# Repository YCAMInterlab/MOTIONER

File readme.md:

# MOTIONER

## Open source low cost inertial motion capture system.

MOTIONER is a low cost inertial motion capture system developed for Reactor for Awareness in Motion(RAM) project at Yamaguchi Center for Arts in Media (YCAM). Using MOTIONER, you can capture, record and playback body movements, and send the data via OSC messages over a network. MOTIONER is designed to work with RAM Dance Toolkit using openFrameworks, and will work with creative coding environments that provide OSC. MOTIONER is developed in collaboration with Yoko Ando (The Forsythe Company) and other dancers. MOTIONER is a light weight, low-stress, and low latency system. Because it's an inertial system, the sensors can be attached either inside or on the outside of clothing.

For more details, please see [MOTIONER wiki](https://github.com/YCAMInterlab/MOTIONER/wiki/)

詳しい情報は[MOTIONER wiki](https://github.com/YCAMInterlab/MOTIONER/wiki/)を参照してください。

## Licenses

### Application
MOTIONER software by YCAM InterLab and Yoshito Onishi is licensed under the 
[Apache License, Version2.0](http://www.apache.org/licenses/LICENSE-2.0.html)

    Copyright 2012-2013 YCAMInterLab and Yoshito Onishi

    Licensed under the Apache License, Version 2.0 (the "License");
    you may not use this file except in compliance with the License.
    You may obtain a copy of the License at

       http://www.apache.org/licenses/LICENSE-2.0

    Unless required by applicable law or agreed to in writing, software
    distributed under the License is distributed on an "AS IS" BASIS,
    WITHOUT WARRANTIES OR CONDITIONS OF ANY KIND, either express or implied.
    See the License for the specific language governing permissions and
    limitations under the License.

### Arduino, Processing sketch and mbed code

Copyright 2012-2013 YCAMInterLab and Yoshito Onishi

MOTIONER Arduino, Processing sketch and mbed code by YCAM InterLab and Yoshito Onishi are licensed under the 
[GNU GPL(General Public License) v3.0](http://www.gnu.org/licenses/gpl.html)

### Hardware

<br /><span xmlns:dct="http://purl.org/dc/terms/" property="dct:title">MOTIONER hardware related documents (Schematics, Eagle files, Solder Stencil Mask, Drawing of MOTIONER base, MOTIONER pcb board, vacuum case and strap)</span> by <a xmlns:cc="http://creativecommons.org/ns#" href="http://interlab.ycam.jp/projects/ram" property="cc:attributionName" rel="cc:attributionURL">YCAM InterLab, Yoshito Onishi</a> is licensed under a <a rel="license" href="http://creativecommons.org/licenses/by-sa/4.0/">Creative Commons Attribution-ShareAlike 4.0 International License</a>.

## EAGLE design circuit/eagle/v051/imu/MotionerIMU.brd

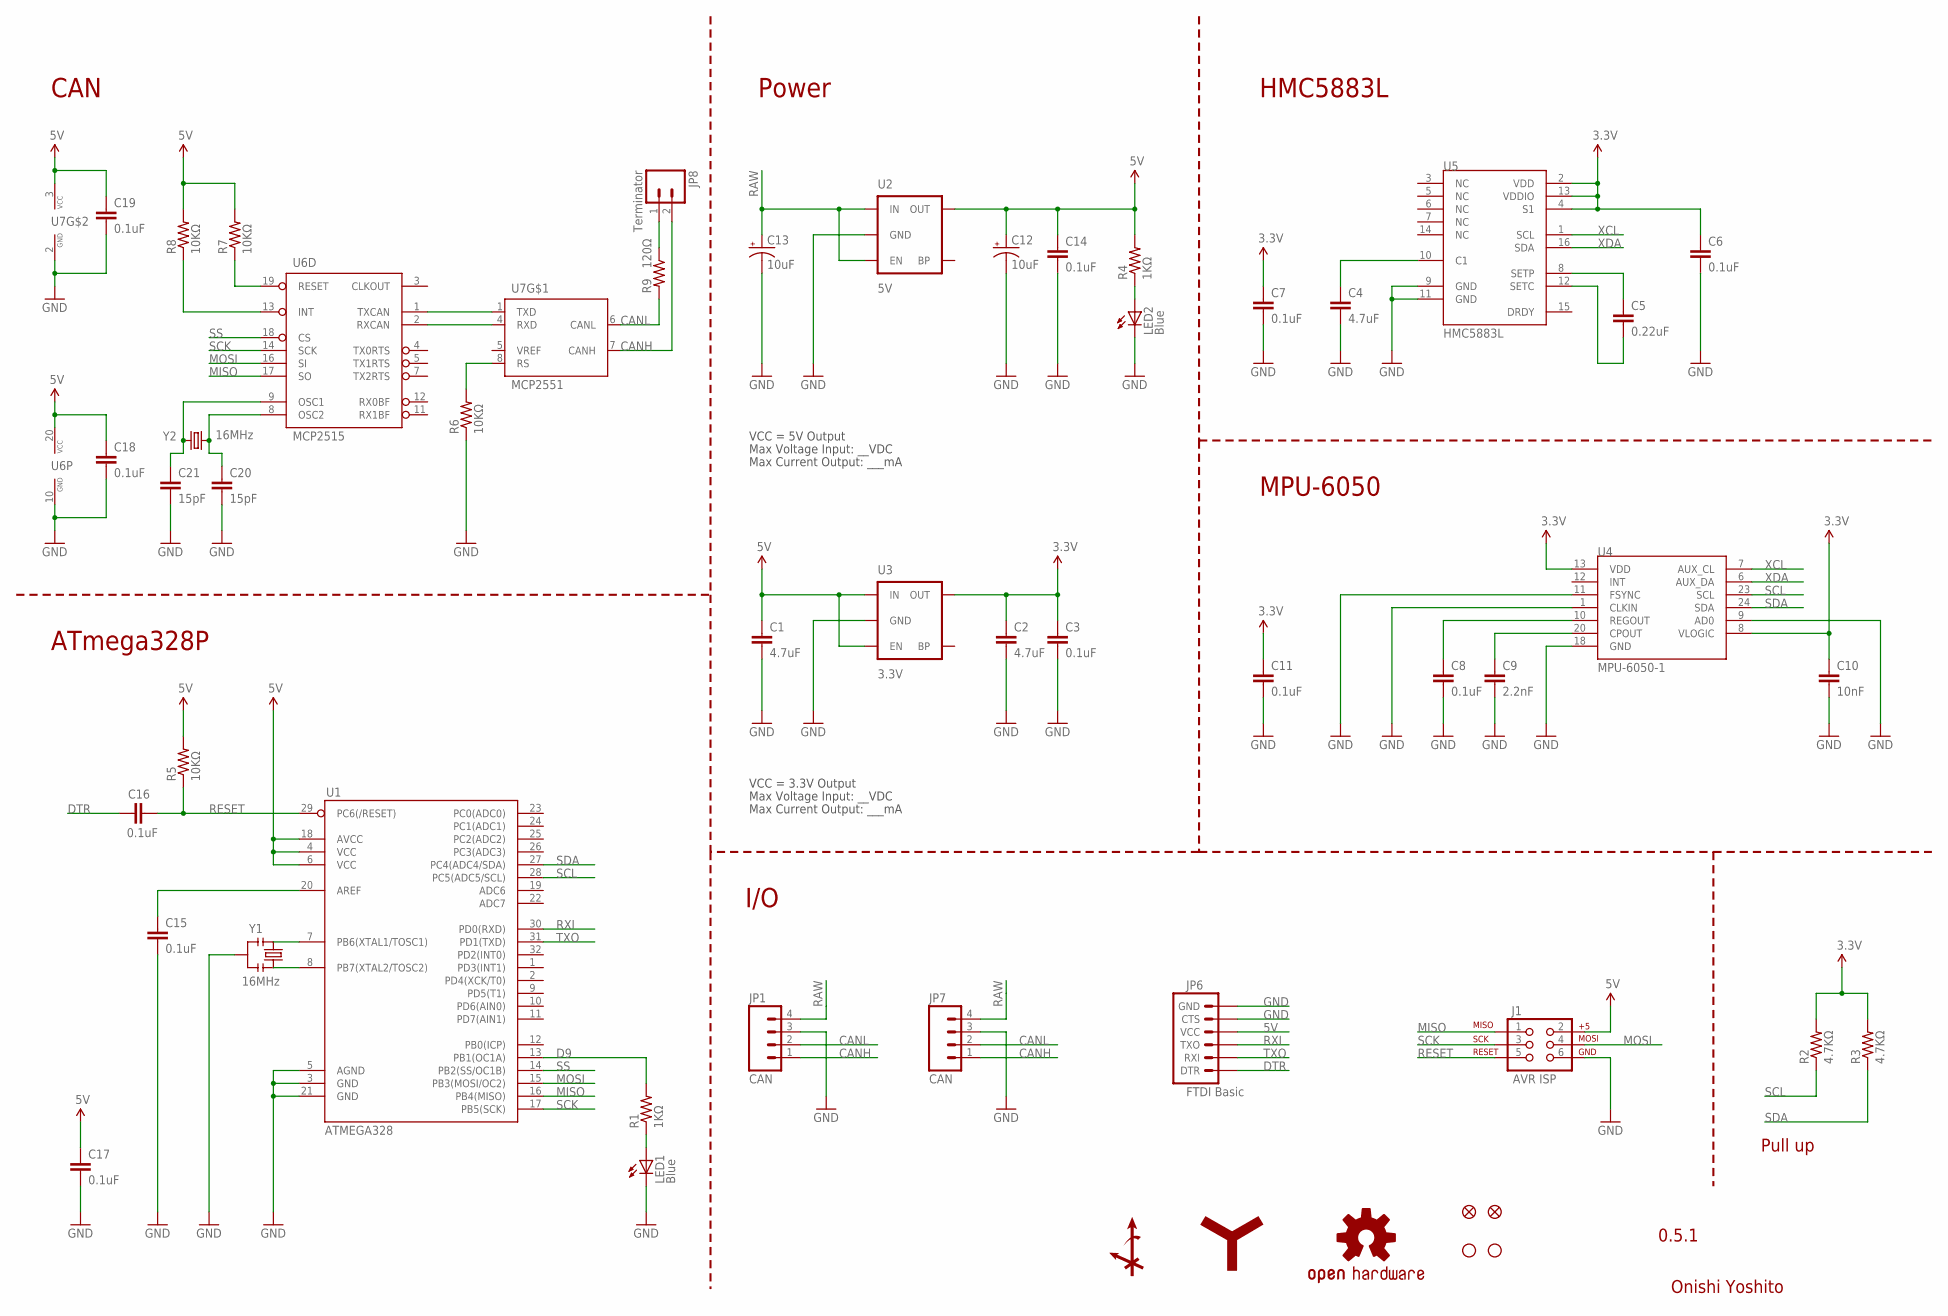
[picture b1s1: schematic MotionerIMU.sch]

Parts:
C1, C2, C4: 4.7uF; 0402-CAP
C3, C6, C7, C8, C11, C14, C15, C16, C17, C18, C19: 0.1uF; 0402-CAP
C5: 0.22uF; 0402-CAP
C9: 2.2nF; 0402-CAP
C10: 10nF; 0402-CAP
C12, C13: 10uF; EIA3216
C20, C21: 15pF; 0402-CAP
J1: AVR ISP; 2X3-NS
JP1, JP7: CAN; JST-4-PTH
JP2, JP5: FIDUCIALUFIDUCIAL; MICRO-FIDUCIAL
JP3, JP4: STAND-OFFTIGHT; STAND-OFF-TIGHT
JP6: FTDI Basic; 1X06
JP8: Terminator; 1X02
LED1, LED2: Blue; LED-0603
R1, R4: 1KΩ; 0402-RES
R2, R3: 4.7KΩ; 0402-RES
R5, R6, R7, R8: 10KΩ; 0402-RES
R9: 120Ω; 0402-RES
U1: ATMEGA328; TQFP32-08
U2: 5V; SOT23-5
U3: 3.3V; SOT23-5
U4: MPU-6050-1; QFN-24-4MM2
U5: HMC5883L; 16LPCC
U6: MCP2515; TSSOP20
U7: MCP2551; SO08
U$2: OSHW-LOGOS; OSHW-LOGO-S
U$11: AXIS-ANGLE_S
U$13: YCAM_LOGO_L
Y1: 16MHz; RESONATOR-SMD
Y2: 16MHz; CRYSTAL-SMD-5X3

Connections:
3.3V: C2.1, C3.1, C6.1, C7.1, C10.1, C11.1, R2.2, R3.2, U3.5 (OUT), U4.8 (VLOGIC), U4.13 (VDD), U5.2 (VDD), U5.4 (S1), U5.13 (VDDIO)
5V: C1.1, C12.A (+), C14.1, C17.1, C18.1, C19.1, J1.2, JP6.4 (VCC), R4.2, R5.2, R7.2, R8.2, U1.4 (VCC), U1.6 (VCC), U1.18 (AVCC), U2.5 (OUT), U3.1 (IN), U3.3 (EN), U6.20 (VCC), U7.3 (VCC)
CANH: JP1.1, JP7.1, JP8.2, U7.7 (CANH)
CANL: JP1.2, JP7.2, R9.2, U7.6 (CANL)
D9: R1.2, U1.13 (PB1(OC1A))
DTR: C16.1, JP6.1 (DTR)
GND: C1.2, C2.2, C3.2, C4.2, C6.2, C7.2, C8.2, C9.2, C10.2, C11.2, C12.C (-), C13.C (-), C14.2, C15.2, C17.2, C18.2, C19.2, C20.2, C21.2, J1.6, JP1.3, JP6.5 (CTS), JP6.6 (GND), JP7.3, LED1.C, LED2.C, R6.1, U1.3 (GND), U1.5 (AGND), U1.21 (GND), U2.2 (GND), U3.2 (GND), U4.1 (CLKIN), U4.9 (AD0), U4.11 (FSYNC), U4.18 (GND), U5.9 (GND), U5.11 (GND), U6.10 (GND), U7.2 (GND), Y1.2
MISO: J1.1, U1.16 (PB4(MISO)), U6.17 (SO)
MOSI: J1.4, U1.15 (PB3(MOSI/OC2)), U6.16 (SI)
unnamed: LED1.A, R1.1
unnamed: LED2.A, R4.1
unnamed: C4.1, U5.10 (C1)
unnamed: C5.1, U5.8 (SETP)
unnamed: C5.2, U5.12 (SETC)
unnamed: C9.1, U4.20 (CPOUT)
unnamed: C8.1, U4.10 (REGOUT)
unnamed: U1.7 (PB6(XTAL1/TOSC1)), Y1.1
unnamed: U1.8 (PB7(XTAL2/TOSC2)), Y1.3
unnamed: C15.1, U1.20 (AREF)
unnamed: U6.1 (TXCAN), U7.1 (TXD)
unnamed: U6.2 (RXCAN), U7.4 (RXD)
unnamed: R6.2, U7.8 (RS)
unnamed: R7.1, U6.19 (RESET)
unnamed: R8.1, U6.13 (INT)
unnamed: C20.1, U6.8 (OSC2), Y2.3 (2)
unnamed: C21.1, U6.9 (OSC1), Y2.1
unnamed: JP8.1, R9.1
RAW: C13.A (+), JP1.4, JP7.4, U2.1 (IN), U2.3 (EN)
RESET: C16.2, J1.5, R5.1, U1.29 (PC6(/RESET))
RXI: JP6.3 (TXO), U1.30 (PD0(RXD))
SCK: J1.3, U1.17 (PB5(SCK)), U6.14 (SCK)
SCL: R2.1, U1.28 (PC5(ADC5/SCL)), U4.23 (SCL)
SDA: R3.1, U1.27 (PC4(ADC4/SDA)), U4.24 (SDA)
SS: U1.14 (PB2(SS/OC1B)), U6.18 (CS)
TXO: JP6.2 (RXI), U1.31 (PD1(TXD))
XCL: U4.7 (AUX_CL), U5.1 (SCL)
XDA: U4.6 (AUX_DA), U5.16 (SDA)

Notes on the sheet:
Onishi Yoshito
0.5.1
HMC5883L
MPU-6050
Pull up
Max Voltage Input: __VDC
Max Current Output: ___mA
VCC = 3.3V Output
VCC = 5V Output
ATmega328P
Power
CAN
I/O

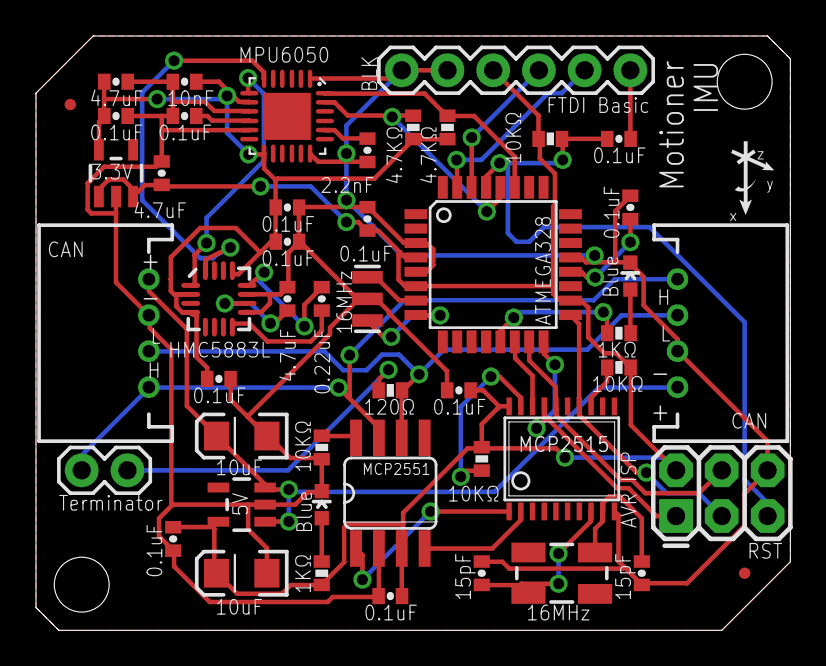
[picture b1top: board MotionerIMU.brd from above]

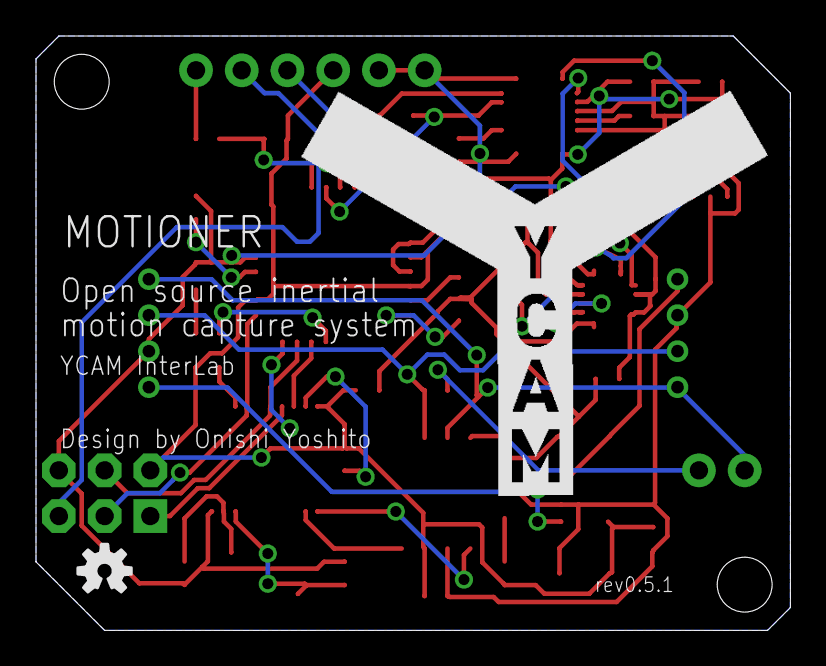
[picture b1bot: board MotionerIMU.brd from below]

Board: 2 copper layers, 41.9 x 33.0 mm, 53 parts (2 on the bottom side), 37 nets.

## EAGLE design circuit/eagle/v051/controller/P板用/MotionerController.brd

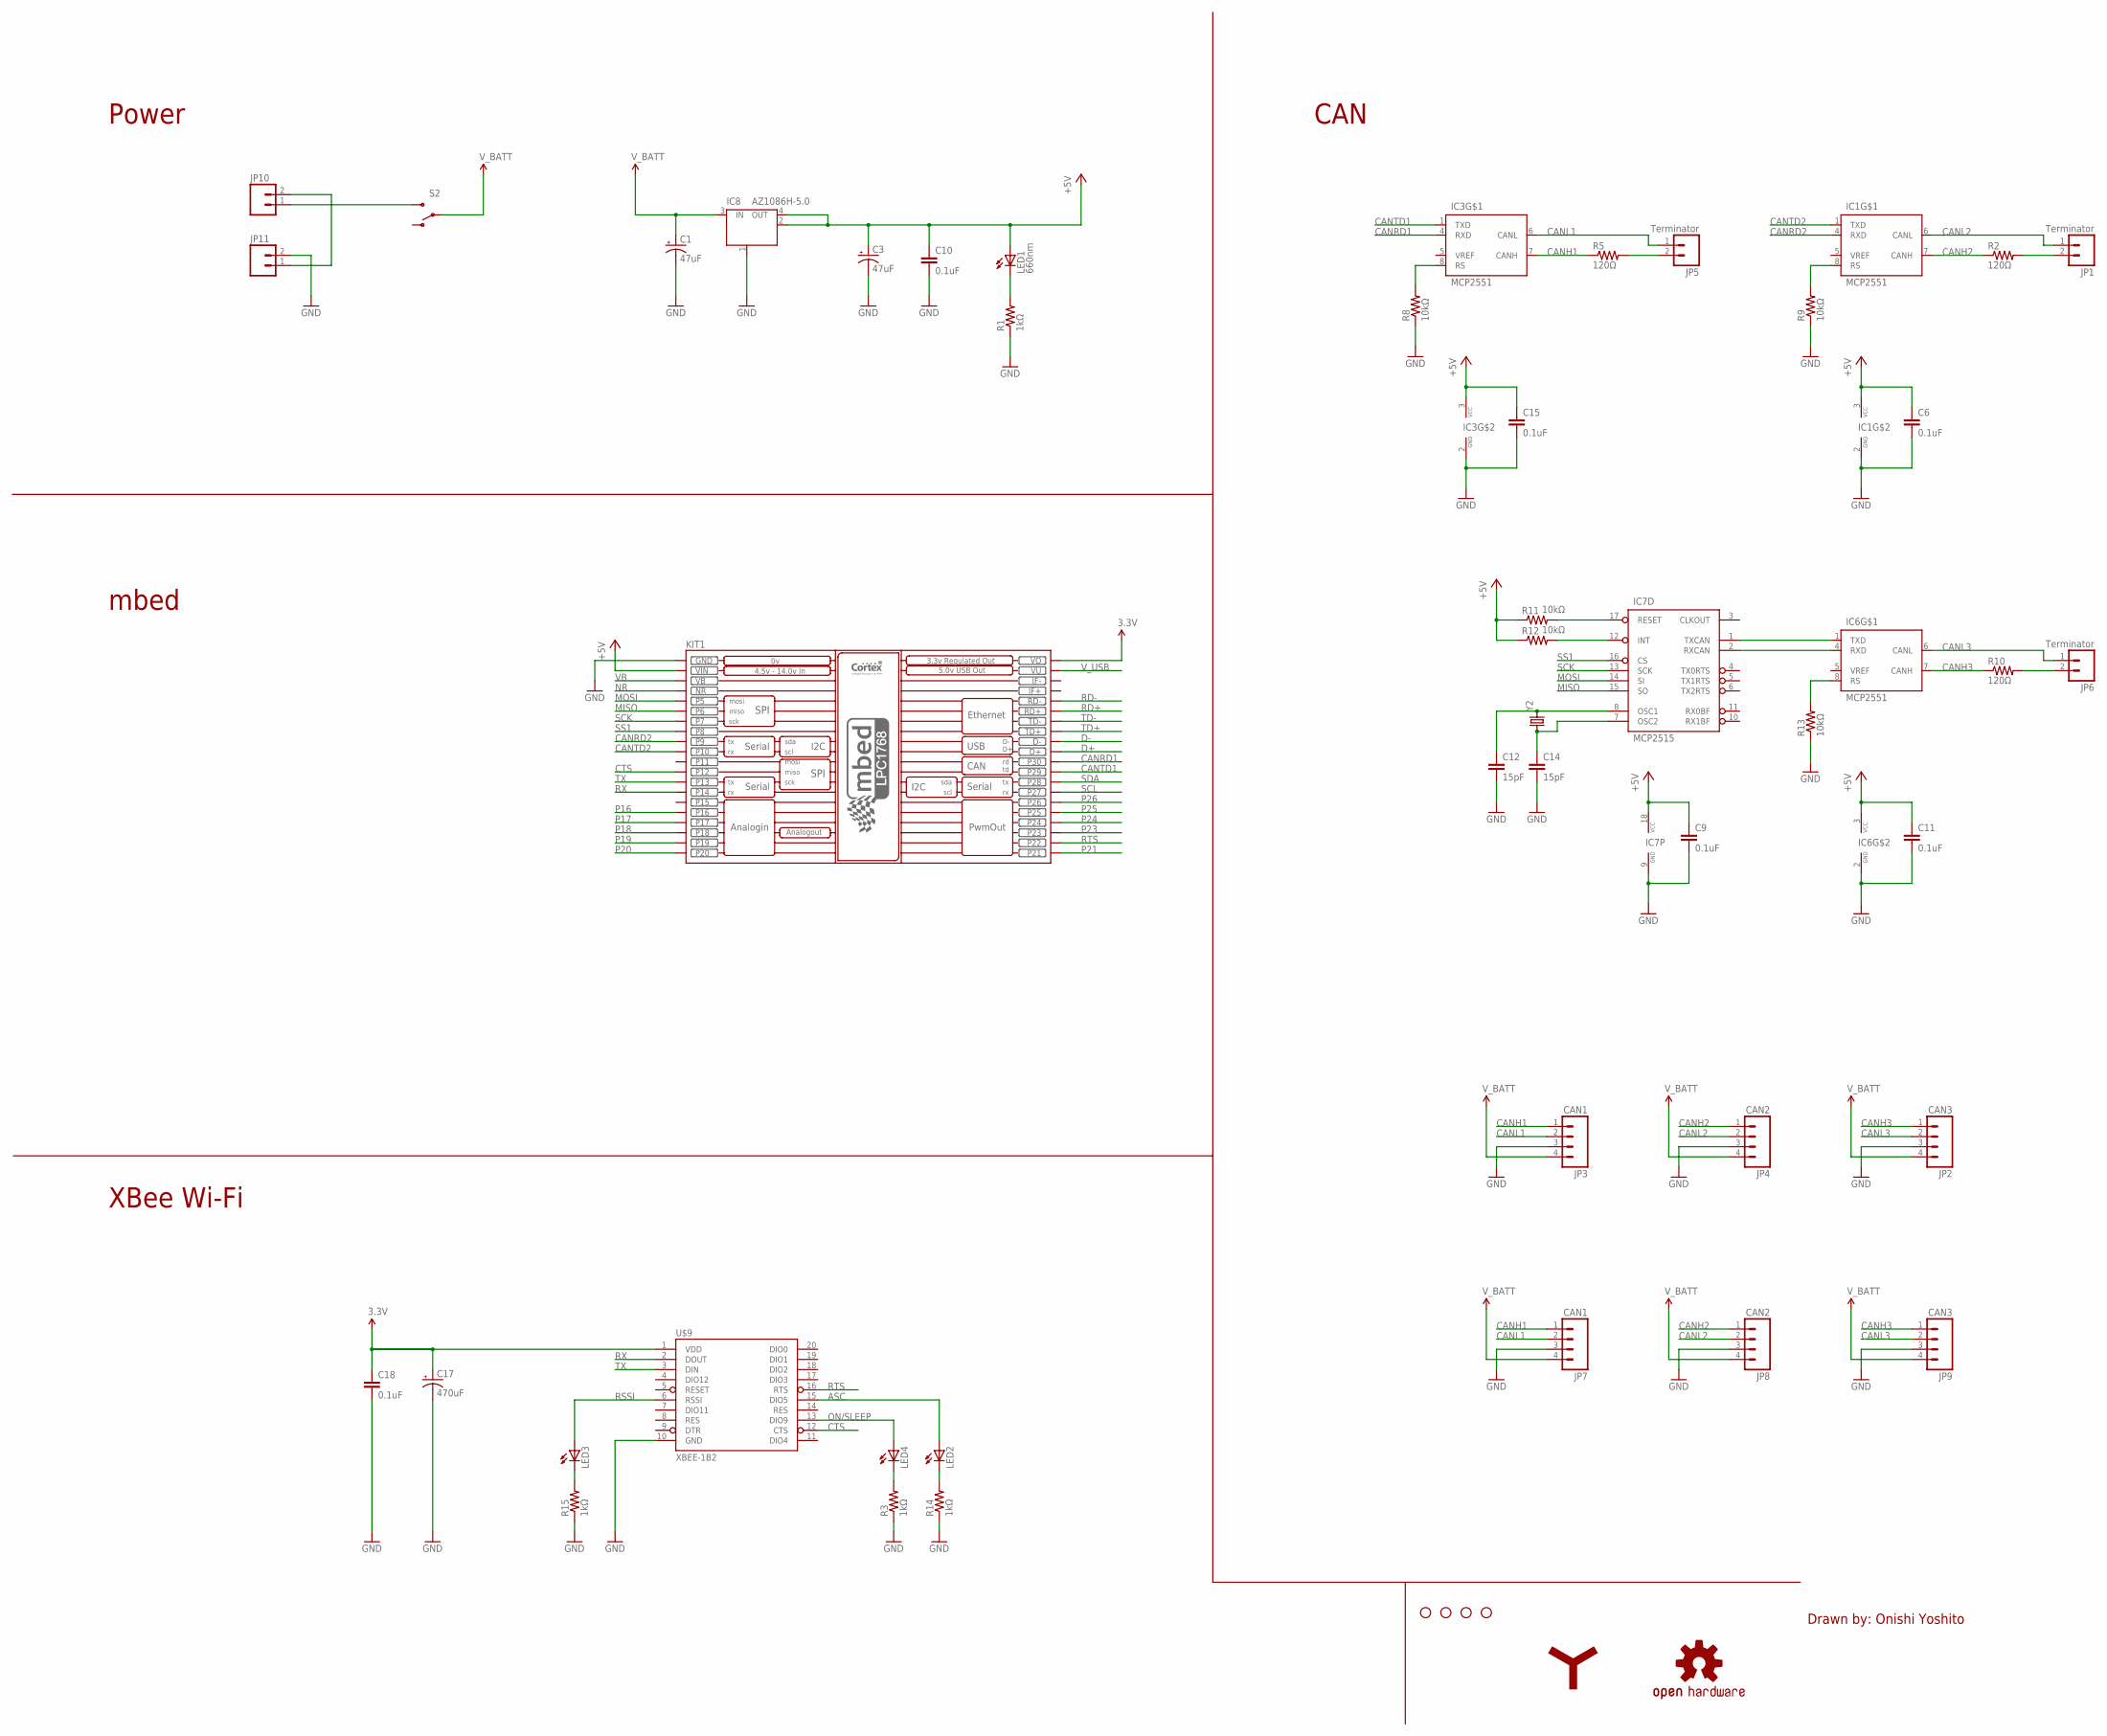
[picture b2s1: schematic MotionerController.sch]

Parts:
C1, C3: 47uF; PANASONIC_D
C6, C9, C10, C11, C15, C18: 0.1uF; 0603-CAP
C12, C14: 15pF; 0603-CAP
C17: 470uF; PANASONIC_G
IC1, IC3, IC6: MCP2551; SO08
IC7: MCP2515; SO-18W
IC8: AZ1086H-5.0; SOT223
JP1, JP5, JP6: Terminator; 1X02
JP2, JP9: CAN3; JST-4-PTH
JP3, JP7: CAN1; JST-4-PTH
JP4, JP8: CAN2; JST-4-PTH
JP10, JP11: M02JST-PTH-2; JST-2-PTH
JP12, JP13, JP15, JP16: STAND-OFF
KIT1: MBED_NXP_LPC1768; MBED-KIT
LED1: 660nm; LED-0603
LED2, LED3, LED4: LED0603; LED-0603
R1, R3, R14, R15: 1kΩ; 0603-RES
R2, R5, R10: 120Ω; 0603-RES
R8, R9, R11, R12, R13: 10kΩ; 0603-RES
S2: SWITCH-SPDTPTH; SWITCH-SPDT
U$9: XBEE-1B2; XBEE-SILK
U$10: YCAM_LOGO_L
U$12: OSHW-LOGOL; OSHW-LOGO-L
Y2: CRYSTAL5X3; CRYSTAL-SMD-5X3

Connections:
3.3V: C17.+, C18.1, KIT1.VOUT (VO), U$9.1 (VDD)
7.4V: C1.+, IC8.3 (IN), JP2.4, JP3.4, JP4.4, JP7.4, JP8.4, JP9.4, S2.2
+5V: C3.+, C6.1, C9.1, C10.1, C11.1, C15.1, IC1.3 (VCC), IC3.3 (VCC), IC6.3 (VCC), IC7.18 (VCC), IC8.2 (OUT), IC8.4 (OUT), KIT1.VIN, LED1.A, R11.1, R12.1
ASC: LED2.A, U$9.15 (DIO5)
CANH1: IC3.7 (CANH), JP3.1, JP7.1, R5.1
CANH2: IC1.7 (CANH), JP4.1, JP8.1, R2.1
CANH3: IC6.7 (CANH), JP2.1, JP9.1, R10.1
CANL1: IC3.6 (CANL), JP3.2, JP5.1, JP7.2
CANL2: IC1.6 (CANL), JP1.1, JP4.2, JP8.2
CANL3: IC6.6 (CANL), JP2.2, JP6.1, JP9.2
CANRD1: IC3.4 (RXD), KIT1.P$30 (P30)
CANRD2: IC1.4 (RXD), KIT1.P$9 (P9)
CANTD1: IC3.1 (TXD), KIT1.P$29 (P29)
CANTD2: IC1.1 (TXD), KIT1.P$10 (P10)
CTS: KIT1.P$12 (P12), U$9.12 (CTS)
D+: KIT1.D+
D-: KIT1.D-
GND: C1.-, C3.-, C6.2, C9.2, C10.2, C11.2, C12.2, C14.2, C15.2, C17.-, C18.2, IC1.2 (GND), IC3.2 (GND), IC6.2 (GND), IC7.9 (GND), IC8.1 (GND/ADJ), JP2.3, JP3.3, JP4.3, JP7.3, JP8.3, JP9.3, JP11.2, KIT1.GND, R1.1, R3.1, R8.1, R9.1, R13.1, R14.1, R15.1, U$9.10 (GND)
MISO: IC7.15 (SO), KIT1.P$6 (P6)
MOSI: IC7.14 (SI), KIT1.P$5 (P5)
unnamed: LED1.C, R1.2
unnamed: LED4.C, R3.2
unnamed: JP10.1, S2.3 (S)
unnamed: IC3.8 (RS), R8.2
unnamed: IC1.8 (RS), R9.2
unnamed: JP1.2, R2.2
unnamed: IC6.1 (TXD), IC7.1 (TXCAN)
unnamed: IC6.4 (RXD), IC7.2 (RXCAN)
unnamed: IC7.12 (INT), R12.2
unnamed: JP5.2, R5.2
unnamed: IC7.17 (RESET), R11.2
unnamed: IC6.8 (RS), R13.2
unnamed: JP6.2, R10.2
unnamed: C12.1, IC7.8 (OSC1), Y2.3 (2)
unnamed: C14.1, IC7.7 (OSC2), Y2.1
unnamed: JP10.2, JP11.1
unnamed: LED3.C, R15.2
unnamed: LED2.C, R14.2
NR: KIT1.NR
ON/SLEEP: LED4.A, U$9.13 (DIO9)
P16: KIT1.P$16 (P16)
P17: KIT1.P$17 (P17)
P18: KIT1.P$18 (P18)
P19: KIT1.P$19 (P19)
P20: KIT1.P$20 (P20)
P21: KIT1.P$21 (P21)
P23: KIT1.P$23 (P23)
P24: KIT1.P$24 (P24)
P25: KIT1.P$25 (P25)
P26: KIT1.P$26 (P26)
RD+: KIT1.RD+
RD-: KIT1.RD-
RSSI: LED3.A, U$9.6 (RSSI)
RTS: KIT1.P$22 (P22), U$9.16 (RTS)
RX: KIT1.P$14 (P14), U$9.2 (DOUT)
SCK: IC7.13 (SCK), KIT1.P$7 (P7)
SCL: KIT1.P$27 (P27)
SDA: KIT1.P$28 (P28)
SS1: IC7.16 (CS), KIT1.P$8 (P8)
TD+: KIT1.TD+
TD-: KIT1.TD-
TX: KIT1.P$13 (P13), U$9.3 (DIN)
VB: KIT1.VB
V_USB: KIT1.VU

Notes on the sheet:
CAN
Power
mbed
XBee Wi-Fi
Drawn by: Onishi Yoshito

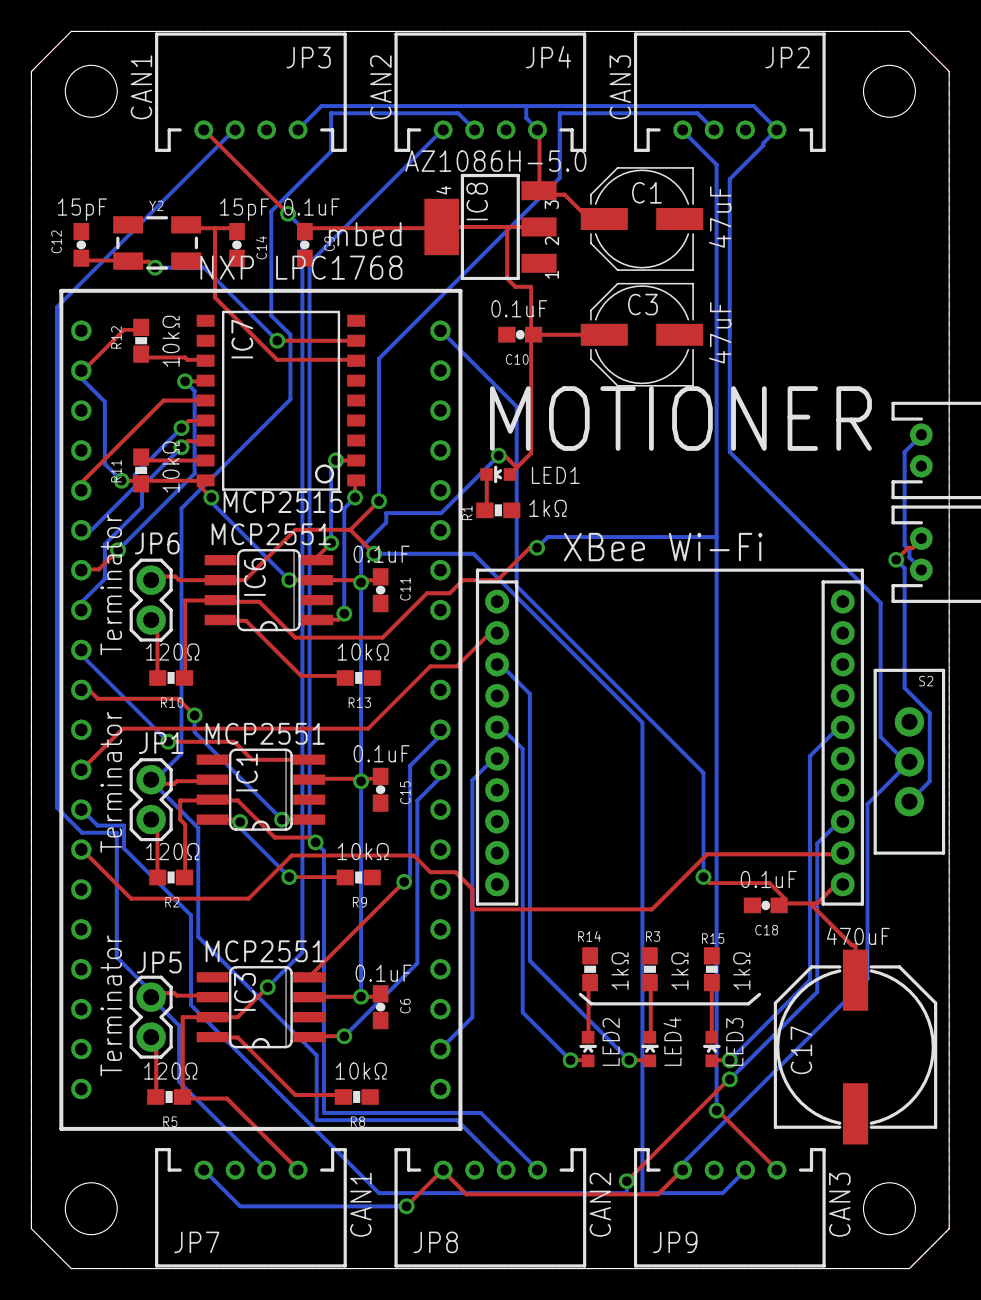
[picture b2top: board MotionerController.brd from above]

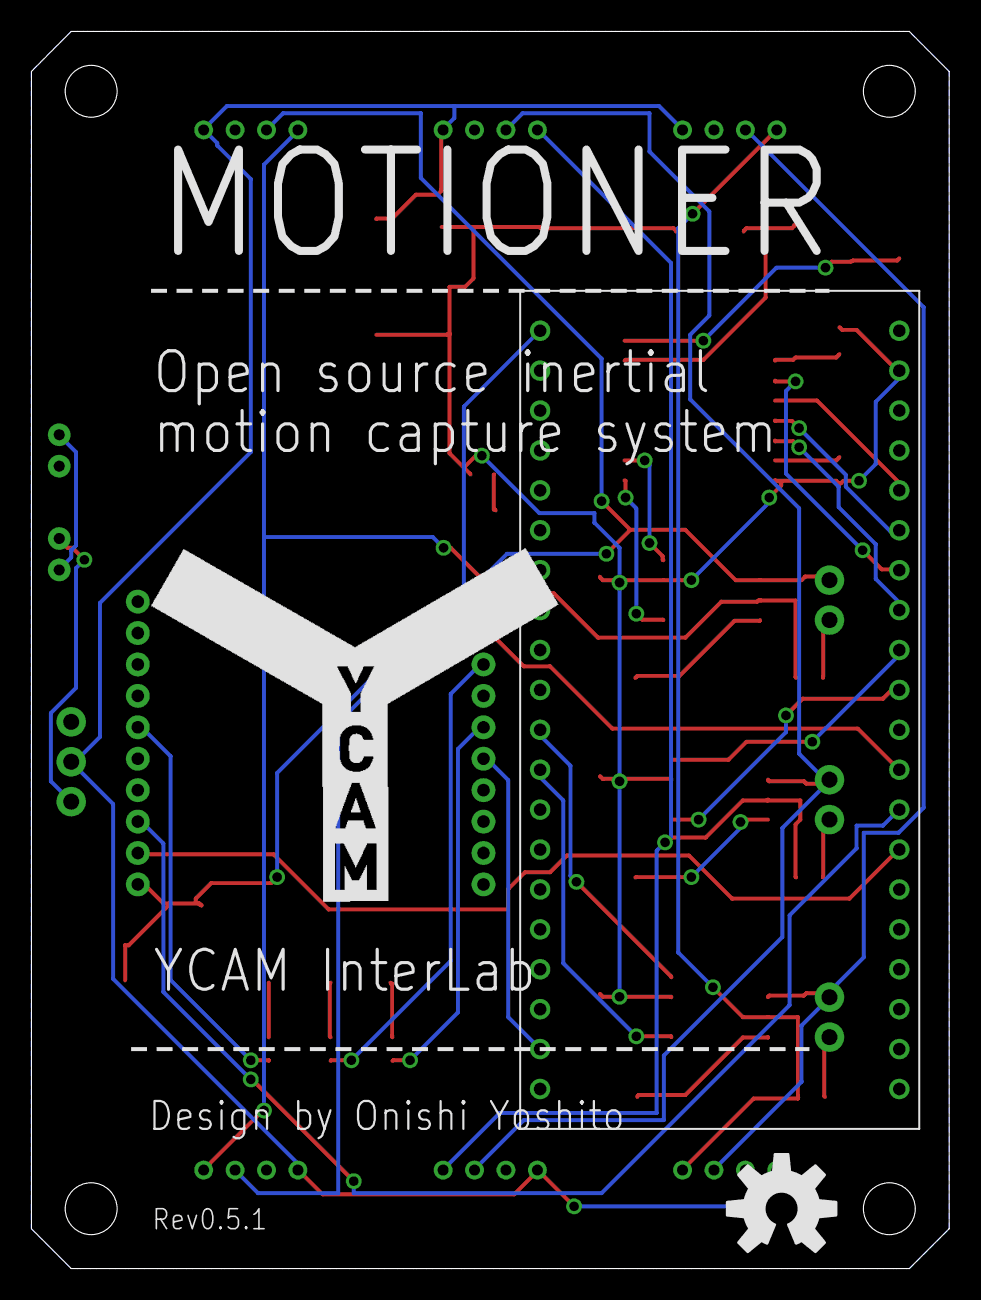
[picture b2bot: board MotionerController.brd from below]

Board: 2 copper layers, 58.4 x 78.7 mm, 53 parts (2 on the bottom side), 43 nets.

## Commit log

2013-03-20 added circuit and some resources
2013-03-21 added P5 sketches
2013-03-21 added an oF project and submodules
2013-03-21 added submodules
2013-03-21 updated submodules.sh
2013-03-22 added shading #oF
2013-04-14 Updated diagrams
2013-04-14 Added XBeeWi-Fi settings file
2013-04-14 Updated xcodeproj. Corresponded to OSX 10.6
2013-04-14 Added Arduino sketches and libraries
2013-04-15 Changed oF app version
2013-04-24 Added embed repo webloc. Updated diagrams.
2013-04-24 Corresponded to Windows #oF
2014-07-14 Load free node structure from XML file
2014-07-17 bugfix: m2
2014-07-17 motionerimu
2014-07-17 remove: motioner controller webloc
2014-07-18 edited xml files
2014-07-18 bugfix
2014-12-19 fix position, external input for absolute position
2015-01-23 Added calling ofRemoveListner
2015-02-02 .gitkeep data/motion/mot directory
2015-02-04 Disable escape quit app
2015-02-04 Brushed up UI
2015-02-04 Removed camera control tool
2015-02-04 Updated inspector
2015-02-04 Changed grid looks, removed show joint name func
2015-02-04 Bugfix for GLFW file dialog: differed loading file
2015-02-04 Updated xml settings
2015-02-04 Bugfix: selecting skeleton with UI
2015-02-04 Updated visual
2015-02-05 Updated tabbed canvas
2015-02-05 Removed ofxGLUtils
2015-02-05 Updated submodules
2015-02-05 Deleted ofxGLUtils
2015-02-05 Removed addon
2015-02-05 Updated project
2015-02-05 Removed test skeletons
2015-02-05 Removed log
2015-02-05 Updated disable joints
2015-02-05 Visualizing node which has no responce
2015-02-05 Create motion data dir when it dosen't exists
2015-02-05 Added setting color function
2015-02-06 Updated logger and inculde it into release build
2015-02-06 Added LR label to skeleton
2015-02-06 Bugfix: initializing textures
2015-02-06 Changed UI letters to Upper camel case
2015-02-06 Changed enable osc toggle
2015-02-06 Disabled end site
2015-02-06 Bugfix: error visualization
2015-02-07 New clean XML format
2015-02-07 Changed UI toggle type
2015-02-08 Cleanup
2015-02-08 Updated .gitmodules
2015-02-09 Updated mobed program and added controller setting
2015-02-11 Updated .gitignore
2015-02-11 Bugfix for Win
2015-02-11 Added vs2012 project
2015-02-11 Updated ofxException
2015-02-17 Bugfix file loading for Win
2015-07-21 made longer soldering pads for the HMC5883L

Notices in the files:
parts and their libraries:
SparkFun-LED: Licensing: CC v3.0 Share-Alike You are welcome to use this library for commercial purposes.
